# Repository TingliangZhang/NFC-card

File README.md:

# NFC-card
NFC Business Card

参考

https://www.instructables.com/PCB-Business-Card-With-NFC/

## 元件选型

NFC Tag

NT3H1101W0FHKH / NT3H2111W0FHKH

https://www.nxp.com/part/NT3H2111W0FHK#/

XQFP没封装

换用

https://www.nxp.com/part/NT3H2111W0FT1#/

https://www.nxp.com/part/NT3H2111W0FTT#/

[TSSOP8](https://www.nxp.com/packages/SOT505-1)封装更薄，用NT3H2111W0FTT

https://www.digikey.cn/product-detail/zh/nxp-usa-inc/NT3H2111W0FTTJ/568-12902-1-ND/5872987?keywords=NT3H2111W0FTTJ

100	4.82480

## 尺寸

标准尺寸

85.6mm×54.0mm×1.0mm

## 天线设计

https://github.com/lachlanA/eagle-to-kicad

导入太麻烦了

用EAGEL导出DXF再用AutoCAD去掉焊盘等（可到Kicad里面编辑），导入到KiCad封装编辑器里面，但是没办法作为铜层，所以直接编辑源码

把F.Adhes全部替换为F.Cu

搞定

## PCB视频

https://www.bilibili.com/video/BV1dK4y1s72o

https://www.jlc.com/portal/factoryVideo/0/0

## 讲座需要Win软件：

腾讯会议

Powerpoint

Altium Designer 20+

KiCad 6.1+

Apowerec录屏

嘉立创下单小助手

## 换用Mac后：

使用 QuickTime Player录屏

https://support.apple.com/zh-cn/HT208721

安装时把kicad文件夹拷到libraries/application support里面需要授权。最好直接拖到文件夹里面而非快捷方式，这样才能链接库。

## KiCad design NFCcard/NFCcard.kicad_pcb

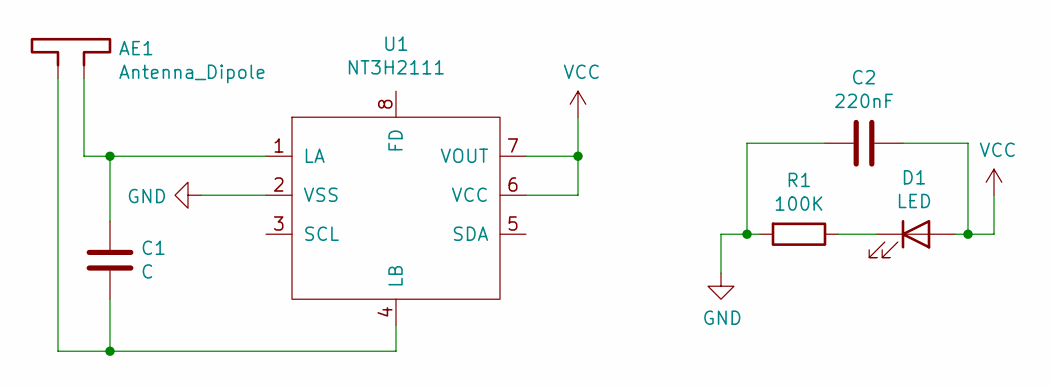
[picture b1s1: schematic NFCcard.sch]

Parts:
AE1: Antenna_Dipole; NFCantenna
C1: C; C_0603_1608Metric
C2: 220nF; C_0603_1608Metric
D1: LED; LED_0603_1608Metric
R1: 100K; C_0603_1608Metric
U1: NT3H2111; TSSOP-8_3x3mm_P0.65mm

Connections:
GND: C2.2, R1.2, U1.2 (VSS)
unnamed: AE1.1, C1.1, U1.4 (LB)
unnamed: AE1.2, C1.2, U1.1 (LA)
unnamed: D1.1 (K), R1.1
VCC: C2.1, D1.2 (A), U1.6 (VCC), U1.7 (VOUT)

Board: 2 copper layers, 6 parts (0 on the bottom side), 5 nets, no tracks yet.

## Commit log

2020-10-15 NT3H2111
2020-10-15 Ini Pro
2020-10-15 TSSOP-8
2020-10-15 Import
2020-10-15 Finnally Imported
2020-10-16 Layout
